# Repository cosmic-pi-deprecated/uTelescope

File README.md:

# uTelescope
A new mini detector developed during the GTI SDG summer school 2017

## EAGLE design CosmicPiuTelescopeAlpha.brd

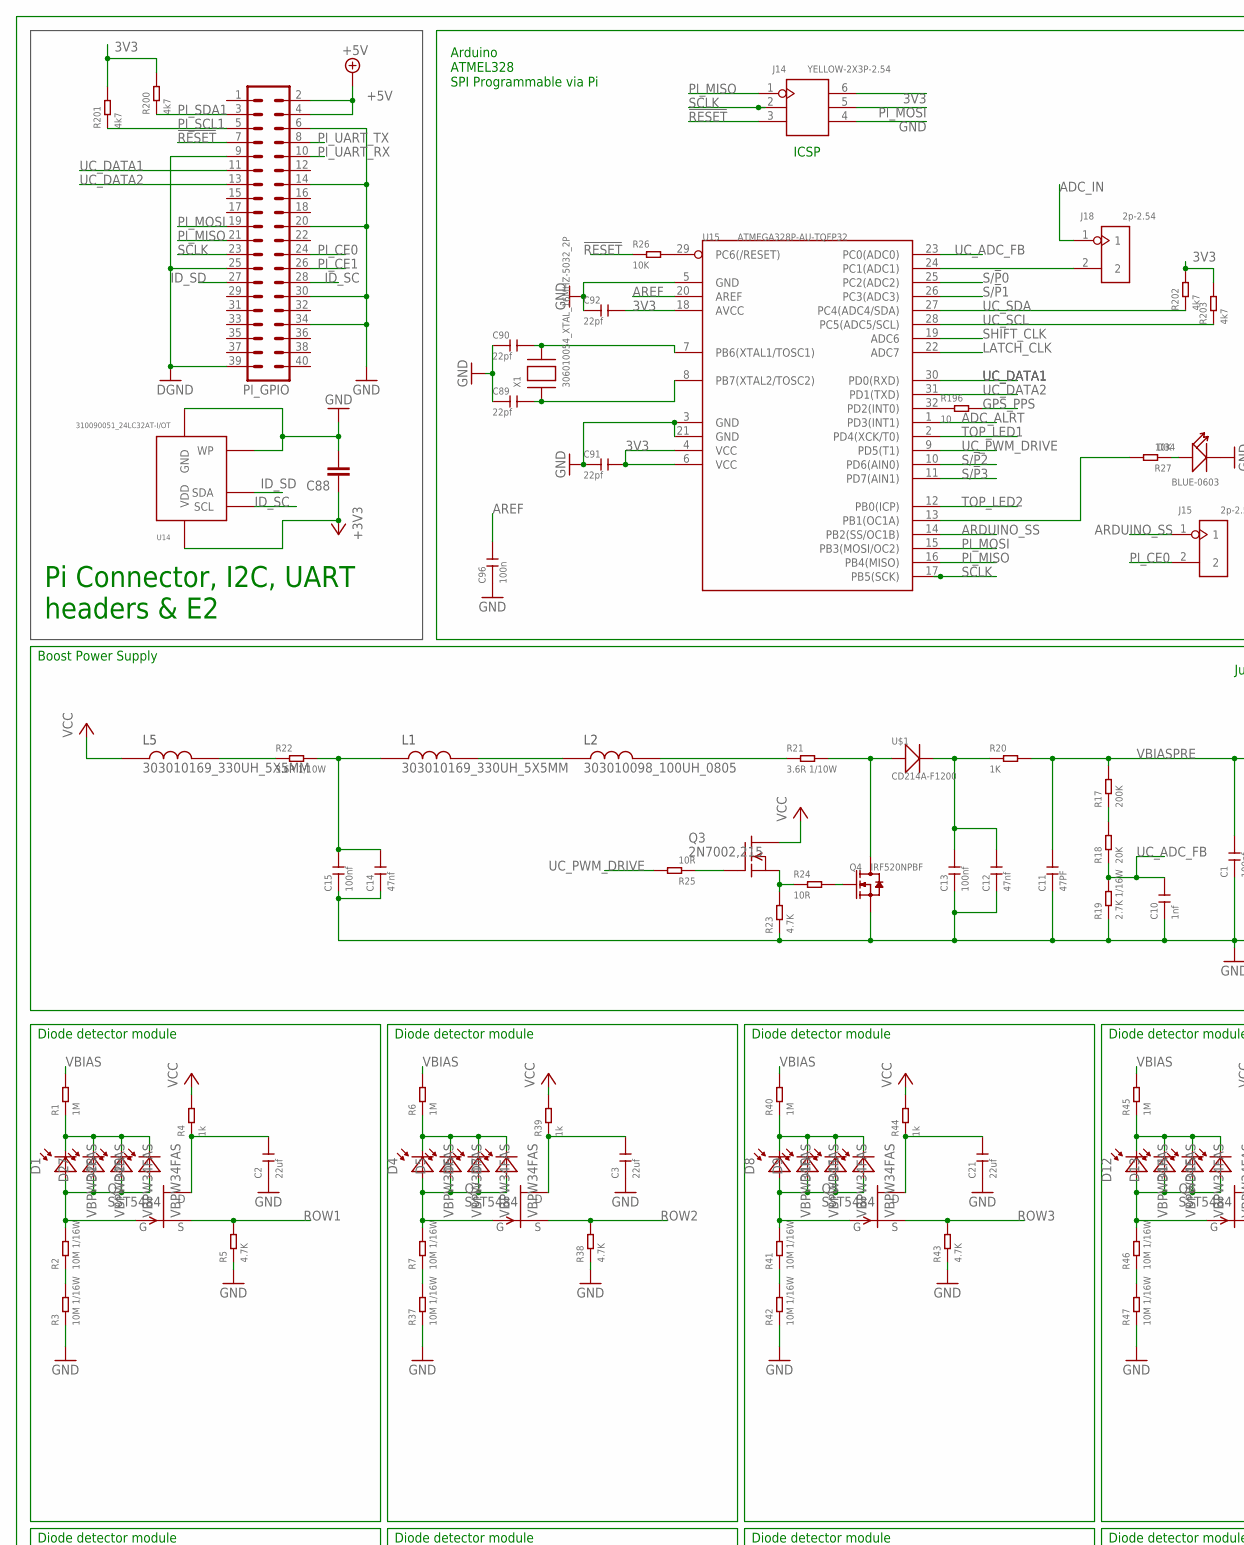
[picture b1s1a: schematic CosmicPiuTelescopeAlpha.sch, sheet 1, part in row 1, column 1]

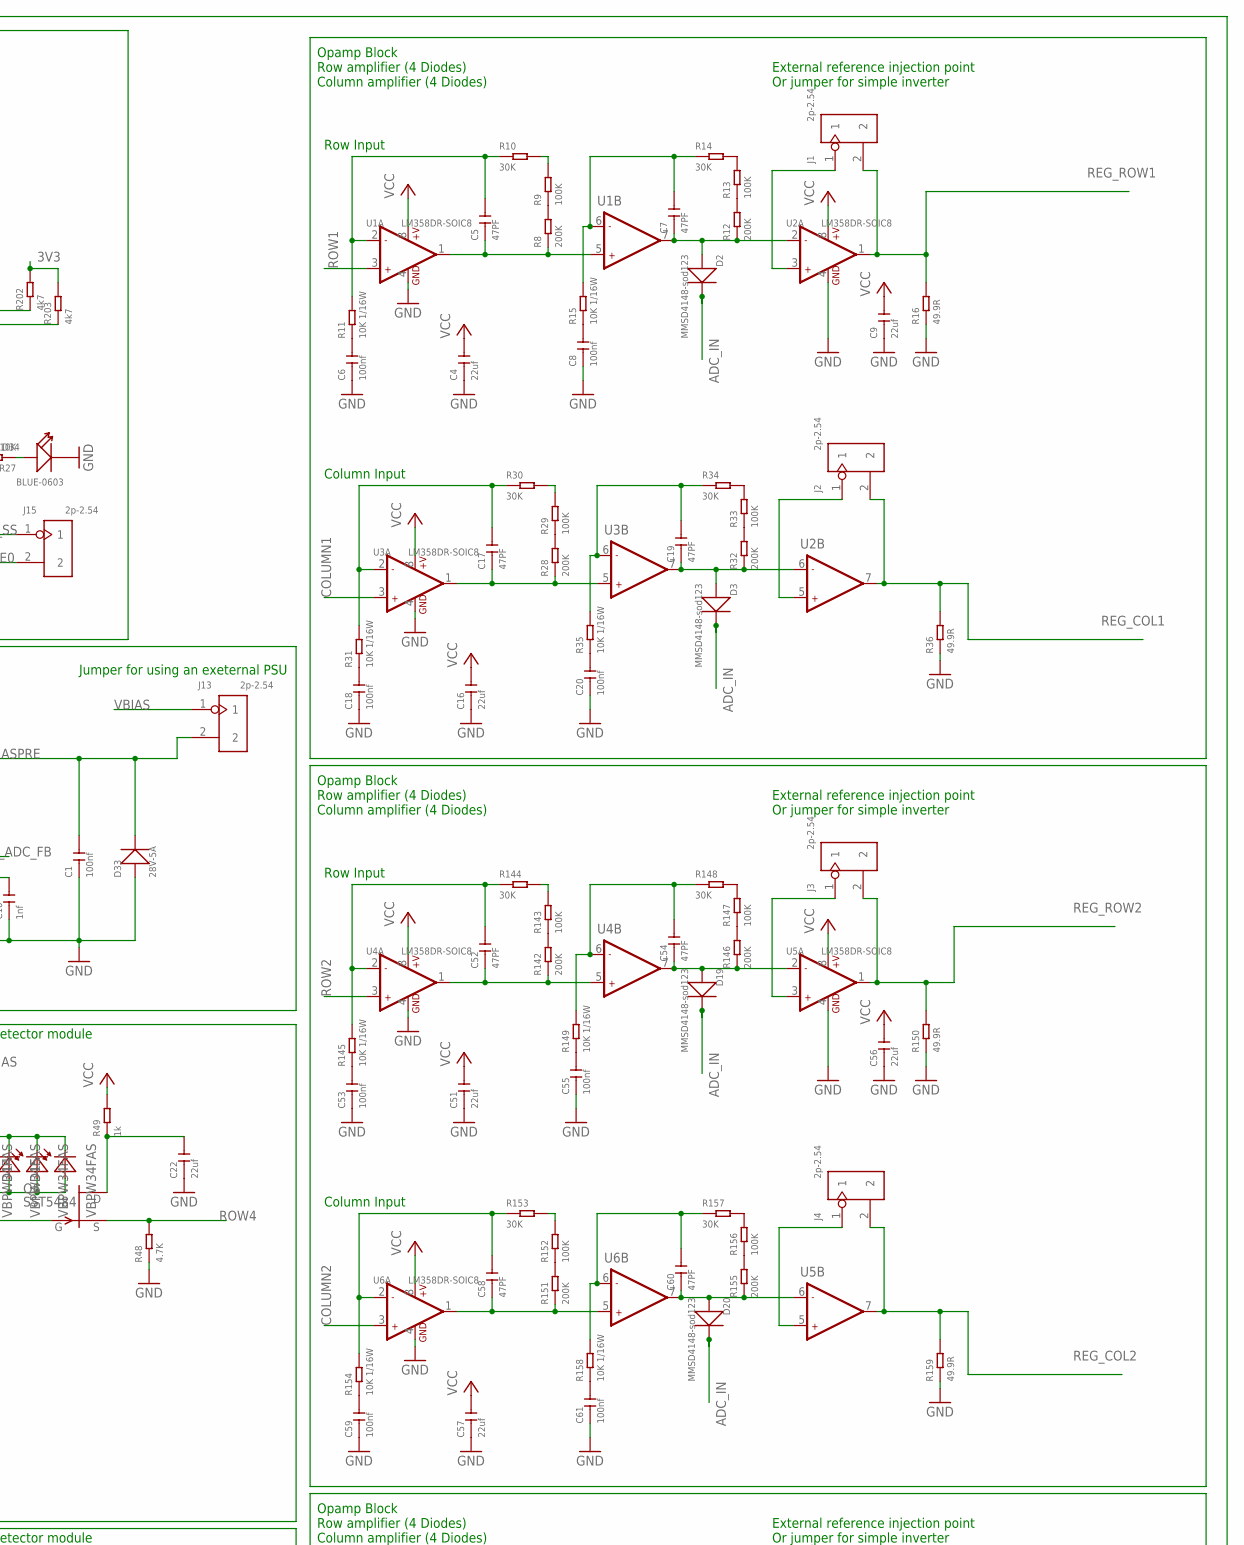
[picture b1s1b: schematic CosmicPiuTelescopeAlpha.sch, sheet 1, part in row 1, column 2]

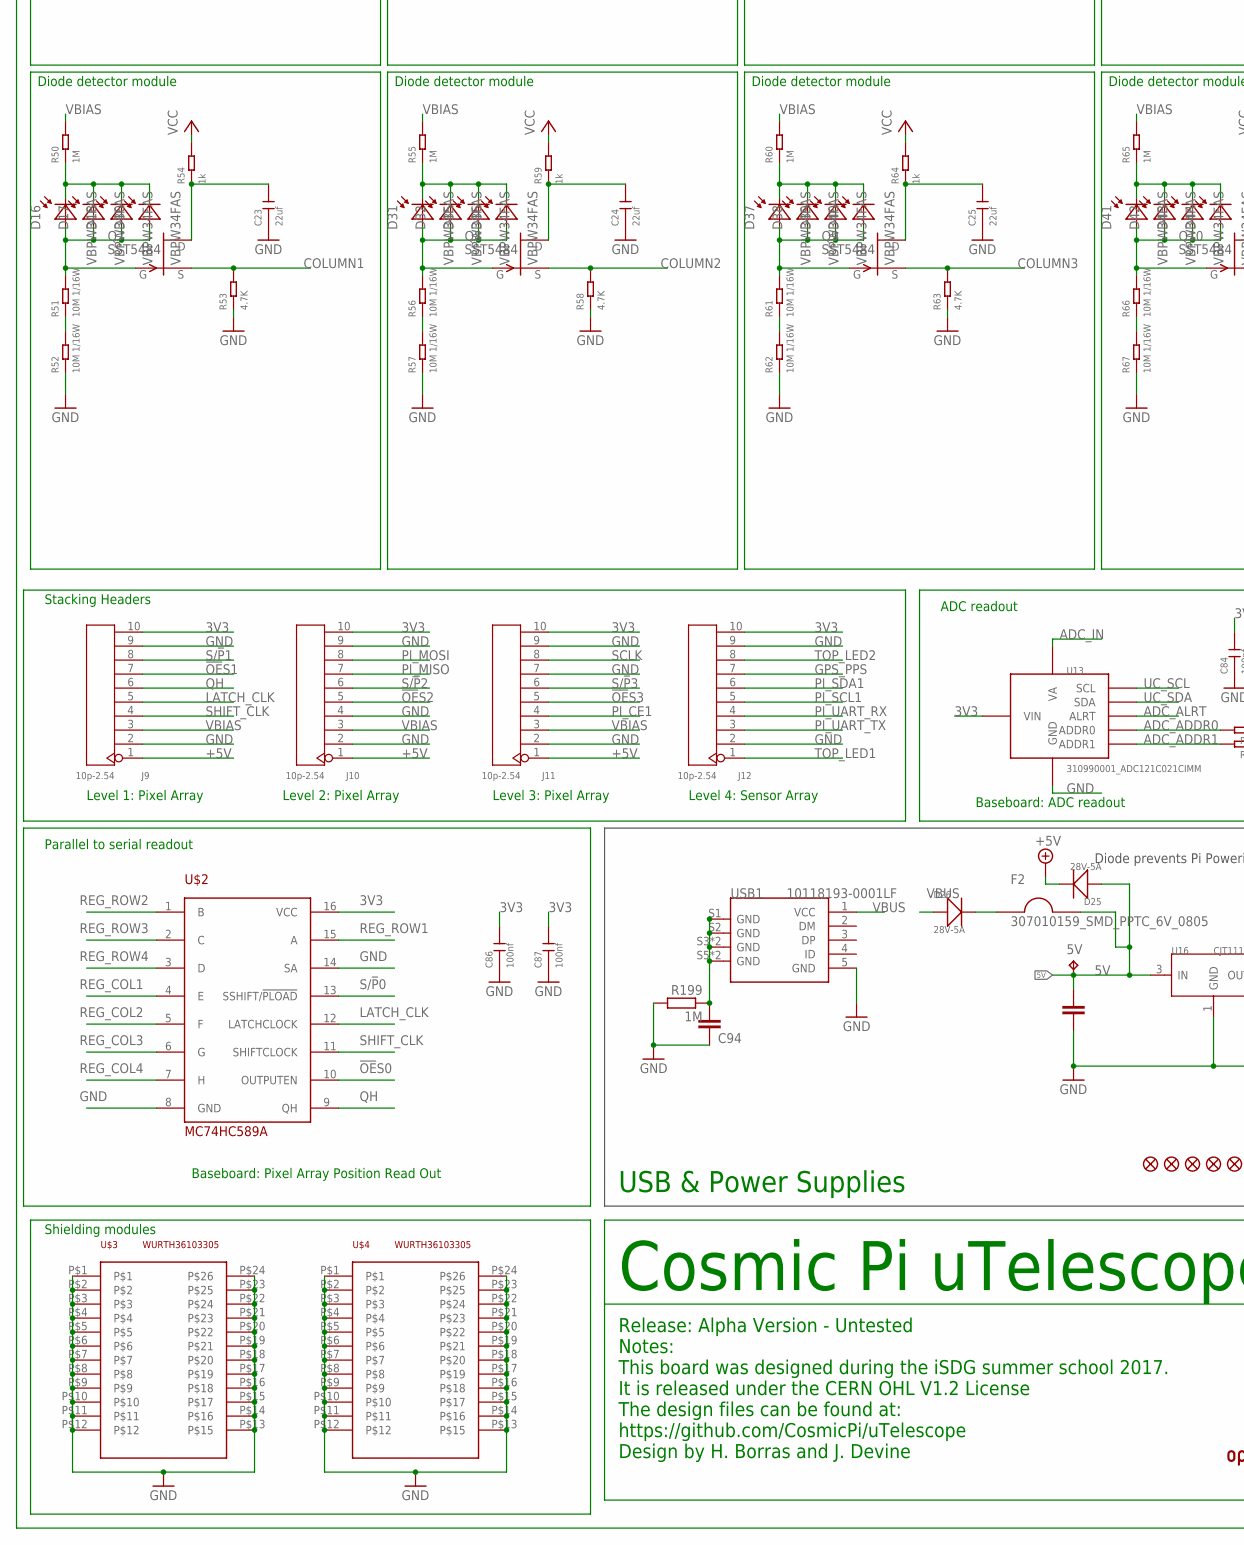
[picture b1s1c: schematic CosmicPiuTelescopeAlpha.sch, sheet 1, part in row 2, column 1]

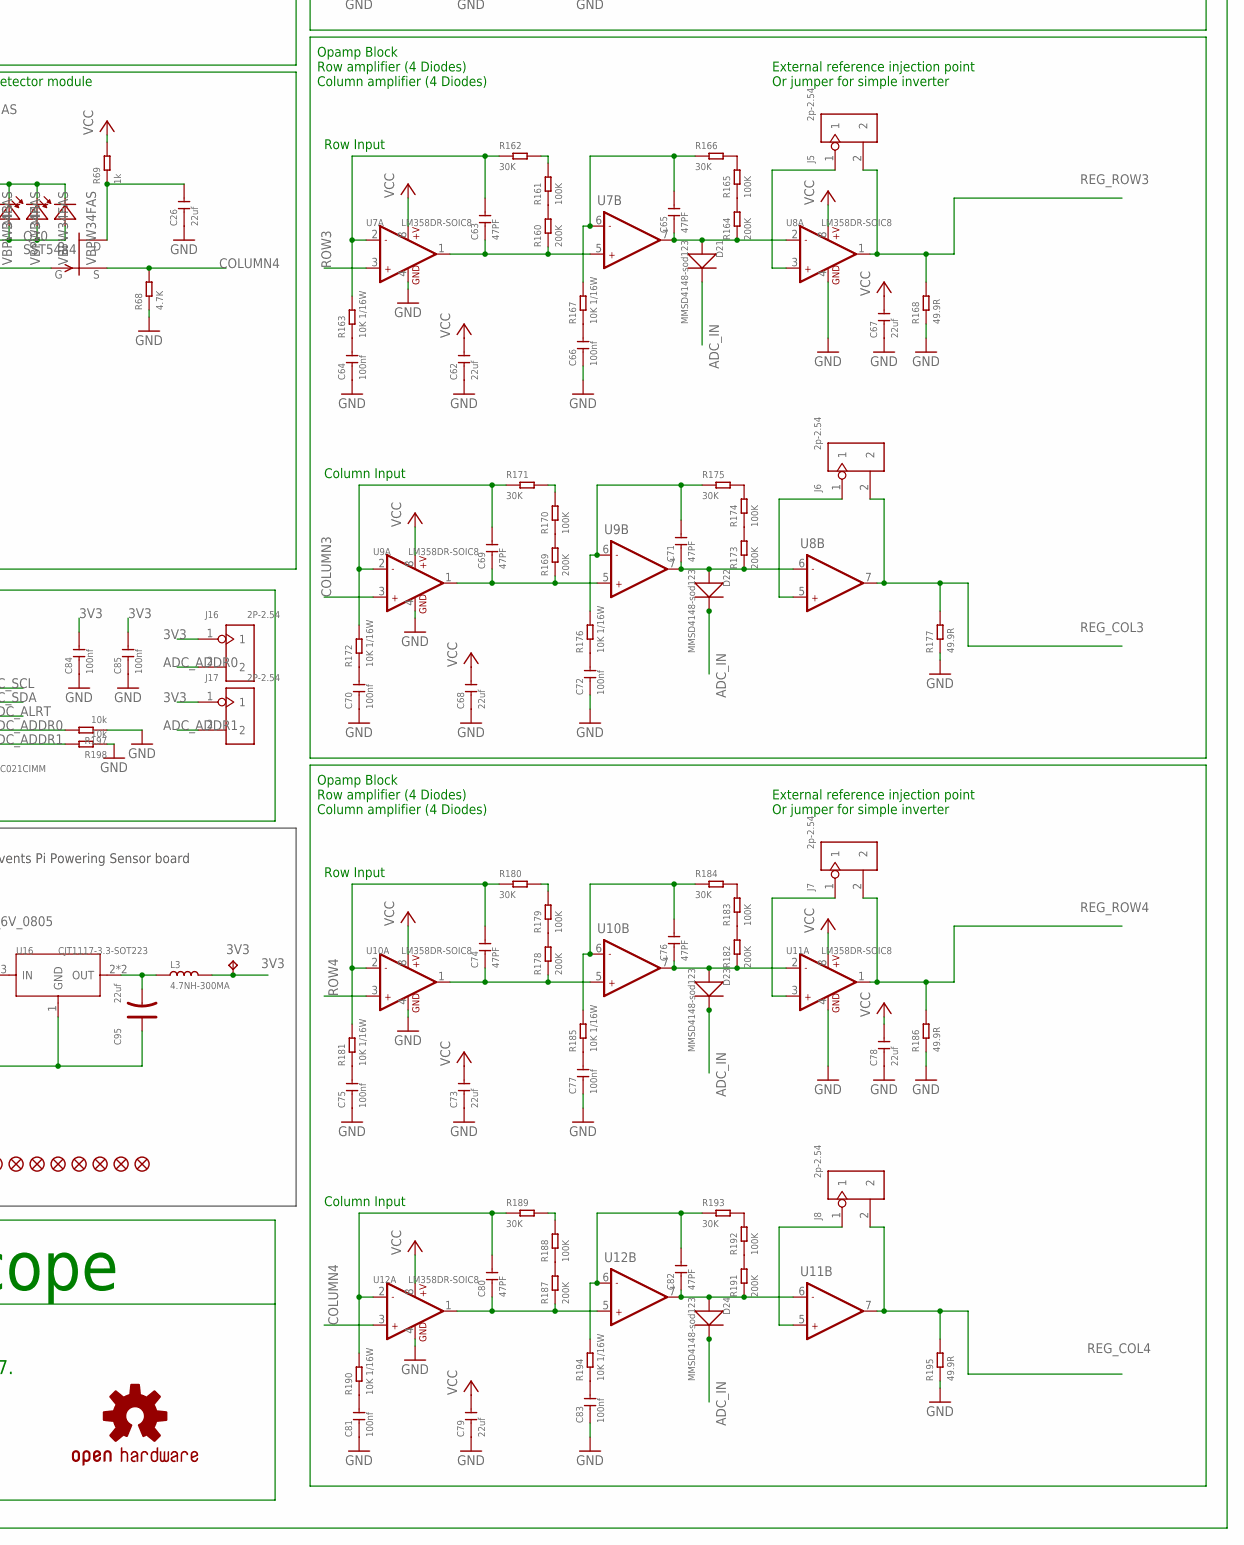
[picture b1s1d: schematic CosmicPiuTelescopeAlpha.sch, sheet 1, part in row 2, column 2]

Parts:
3V3, 5V: TPB1,27; B1,27
C1, C13, C15: 100nf; C0603
C2, C3, C21, C22, C23, C24, C25, C26: 22uf; C1206
C4, C9, C16, C51, C56, C57, C62, C67, C68, C73, C78, C79: 22uf; C0805
C5, C7, C11, C17, C19, C52, C54, C58, C60, C63, C65, C69, C71, C74, C76, C80, C82: 47PF; C0402
C6, C8, C18, C20, C53, C55, C59, C61, C64, C66, C70, C72, C75, C77, C81, C83: 100nf; C0402
C10: 1nf; C0603
C12, C14: 47nf; C0402
C84, C85, C86, C87: 100nf; C1206
C88, C94: C-EUC0402; C0402
C89, C90, C91, C92: 22pf; C0603
C93: 47uF; 1206
C95: 22uf; AVX-B
C96: 100n; C0603
D1, D4, D5, D6, D7, D8, D9, D10, D11, D12, D13, D14, D15, D16, D17, D18, D27, D28, D29, D30, D31, D32, D35, D36, D37, D38, D39, D40, D41, D42, D43, D44: VBPW34FAS; SOD6439X130N
D2, D3, D19, D20, D21, D22, D23, D24: MMSD4148-sod123; SOD-123
D25, D26, D33: 28V-5A; DO-214AA
D34: BLUE-0603; LED-0603
F2: 307010159_SMD_PPTC_6V_0805; F0805
FD1, FD2, FD3, FD4, FD5, FD6, FD7, FD8: FIDUCIAL1X2; FIDUCIAL-1X2
J1, J2, J3, J4, J5, J6, J7, J8, J13, J15, J18: 2p-2.54; H2-2.54
J9, J10, J11, J12: 10p-2.54; H10-2.54
J14: YELLOW-2X3P-2.54; H2X3-2.54
J16, J17: 2P-2.54; H2-2.54
L1, L5: 303010169_330UH_5X5MM; L2018
L2: 303010098_100UH_0805; L0805
L3: 4.7NH-300MA; L0402
LOGO1: OSHW-LOGOL; OSHW-LOGO-L
PI_GPIO: MA20-2
Q1, Q2, Q5, Q6, Q7, Q8, Q9, Q10: SST5484; SOT23
Q3: 2N7002,215; SOT23
Q4: IRF520NPBF; TO-220
R1, R6, R40, R45, R50, R55, R60, R65, R199: 1M; R0402
R2, R3, R7, R37, R41, R42, R46, R47, R51, R52, R56, R57, R61, R62, R66, R67: 10M 1/16W; R0402
R4, R39, R44, R49, R54, R59, R64, R69: 1k; R0402
R5, R38, R43, R48, R53, R58, R63, R68: 4.7K; R0402
R8, R12, R17, R28, R32, R142, R146, R151, R155, R160, R164, R169, R173, R178, R182, R187, R191: 200K; R0603
R9, R13, R29, R33, R143, R147, R152, R156, R161, R165, R170, R174, R179, R183, R188, R192: 100K; R0402
R10, R14, R30, R34, R144, R148, R153, R157, R162, R166, R171, R175, R180, R184, R189, R193: 30K; R0603
R11, R15, R31, R35, R145, R149, R154, R158, R163, R167, R172, R176, R181, R185, R190, R194: 10K 1/16W; R0402
R16, R36, R150, R159, R168, R177, R186, R195: 49.9R; R0402
R18: 20K; R0603
R19: 2.7K 1/16W; R0402
R20: 1K; R0603
R21, R22: 3.6R 1/10W; R0603
R23: 4.7K; R0805
R24, R25: 10R; R0603
R26, R27: 10K; R0603
R196: 10; R0603
R197, R198: 10k; R0402
R200, R201, R202, R203: 4k7; R0603
U1, U2, U3, U4, U5, U6, U7, U8, U9, U10, U11, U12: LM358DR-SOIC8; SOIC8-1.27-5X4MM
U13: 310990001_ADC121C021CIMM; VSSOP8
U14: 310090051_24LC32AT-I/OT; SOT235
U15: ATMEGA328P-AU-TQFP32; TQFP32-0.8-7X7MM
U16: CJT1117-3.3-SOT223; SOT-223
U$1: CD214A-F1200; DIOM8059X265N
U$2: MC74HC589A; SOIC127P600X175-16N
U$3, U$4: WURTH36103305; 36103305
USB1: 10118193-0001LF; MICRO-USB5+6P-SMD-0.65-B
X1: 306010054_XTAL_16MHZ-5032_2P; X5032_2P

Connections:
3V3: 3V3.TP, C84.2, C85.2, C86.2, C87.2, C88.1, C91.2, C92.2, J9.10, J10.10, J11.10, J12.10, J14.6, J16.1, J17.1, L3.2, R200.2, R201.2, R202.2, R203.2, U13.P$4 (VIN), U14.4 (VDD), U15.4 (VCC), U15.6 (VCC), U15.18 (AVCC), U$2.16 (VCC)
5V: 5V.TP, C93.1, D25.+, F2.P$2, U16.3 (IN)
!OE!S0: U$2.10 (OUTPUTEN)
!OE!S1: J9.7
!OE!S2: J10.5
!OE!S3: J11.5
!RESET: J14.3, PI_GPIO.7, R26.1
+5V: C4.2, C9.2, C16.2, C51.2, C56.2, C57.2, C62.2, C67.2, C68.2, C73.2, C78.2, C79.2, D25.-, J9.1, J10.1, J11.1, L5.P$1, PI_GPIO.2, PI_GPIO.4, Q3.3 (D), R4.2, R39.2, R44.2, R49.2, R54.2, R59.2, R64.2, R69.2, U1.8 (+V), U2.8 (+V), U3.8 (+V), U4.8 (+V), U5.8 (+V), U6.8 (+V), U7.8 (+V), U8.8 (+V), U9.8 (+V), U10.8 (+V), U11.8 (+V), U12.8 (+V)
ADC_ADDR0: J16.2, R197.2, U13.P$3 (ADDR0)
ADC_ADDR1: J17.2, R198.2, U13.P$6 (ADDR1)
ADC_ALRT: U13.P$2 (ALRT), U15.1 (PD3(INT1))
ADC_IN: D2.-, D3.-, D19.-, D20.-, D21.-, D22.-, D23.-, D24.-, J18.1, U13.P$5 (VA)
ARDUINO_SS: J15.1, U15.14 (PB2(SS/OC1B))
AREF: C96.2, U15.20 (AREF)
COLUMN1: Q7.2 (S), R53.2, U3.3 (+IN1)
COLUMN2: Q8.2 (S), R58.2, U6.3 (+IN1)
COLUMN3: Q9.2 (S), R63.2, U9.3 (+IN1)
COLUMN4: Q10.2 (S), R68.2, U12.3 (+IN1)
GND: C1.1, C2.1, C3.1, C4.1, C6.1, C8.1, C9.1, C10.1, C11.1, C12.1, C13.1, C14.1, C15.1, C16.1, C18.1, C20.1, C21.1, C22.1, C23.1, C24.1, C25.1, C26.1, C51.1, C53.1, C55.1, C56.1, C57.1, C59.1, C61.1, C62.1, C64.1, C66.1, C67.1, C68.1, C70.1, C72.1, C73.1, C75.1, C77.1, C78.1, C79.1, C81.1, C83.1, C84.1, C85.1, C86.1, C87.1, C88.2, C89.1, C90.1, C91.1, C92.1, C93.2, C94.1, C95.+, C96.1, D33.+, D34.-, J9.2, J9.9, J10.2, J10.4, J10.9, J11.2, J11.7, J11.9, J12.2, J12.9, J14.4, PI_GPIO.6, PI_GPIO.9, PI_GPIO.14, PI_GPIO.20, PI_GPIO.25, PI_GPIO.30, PI_GPIO.34, PI_GPIO.39, Q4.2 (S), Q4.HEAT (S), R3.1, R5.1, R16.1, R19.1, R23.1, R36.1, R37.1, R38.1, R42.1, R43.1, R47.1, R48.1, R52.1, R53.1, R57.1, R58.1, R62.1, R63.1, R67.1, R68.1, R150.1, R159.1, R168.1, R177.1, R186.1, R195.1, R197.1, R198.1, R199.2, U1.4 (GND), U2.4 (GND), U3.4 (GND), U4.4 (GND), U5.4 (GND), U6.4 (GND), U7.4 (GND), U8.4 (GND), U9.4 (GND), U10.4 (GND), U11.4 (GND), U12.4 (GND), U13.P$7 (GND), U14.2 (GND), U14.5 (WP), U15.3 (GND), U15.5 (GND), U15.21 (GND), U16.1 (GND), U$2.8 (GND), U$2.14 (SA), U$3.P$1, U$3.P$2, U$3.P$3, U$3.P$4, U$3.P$5, U$3.P$6, U$3.P$7, U$3.P$8, U$3.P$9, U$3.P$10, U$3.P$11, U$3.P$12, U$3.P$13, U$3.P$14, U$3.P$15, U$3.P$16, U$3.P$17, U$3.P$18, U$3.P$19, U$3.P$20, U$3.P$21, U$3.P$22, U$3.P$23, U$3.P$24, U$4.P$1, U$4.P$2, U$4.P$3, U$4.P$4, U$4.P$5, U$4.P$6, U$4.P$7, U$4.P$8, U$4.P$9, U$4.P$10, U$4.P$11, U$4.P$12, U$4.P$13, U$4.P$14, U$4.P$15, U$4.P$16, U$4.P$17, U$4.P$18, U$4.P$19, U$4.P$20, U$4.P$21, U$4.P$22, U$4.P$23, U$4.P$24, USB1.5 (GND)
GPS_PPS: J12.7, R196.2
ID_SC: PI_GPIO.28, U14.1 (SCL)
ID_SD: PI_GPIO.27, U14.3 (SDA)
LATCH_CLK: J9.5, U15.22 (ADC7), U$2.12 (LATCHCLOCK)
unnamed: Q4.3 (D), R21.2, U$1.1 (+)
unnamed: D1.C, D27.C, D28.C, D29.C, R1.1
unnamed: D1.A, D27.A, D28.A, D29.A, Q1.3 (G), R2.2
unnamed: R2.1, R3.2
unnamed: C2.2, Q1.1 (D), R4.1
unnamed: R28.2, R29.1
unnamed: C18.2, R31.1
unnamed: D4.C, D5.C, D6.C, D7.C, R6.1
unnamed: R8.2, R9.1
unnamed: C6.2, R11.1
unnamed: C5.1, R8.1, U1.1 (OUT1), U1.5 (+IN2)
unnamed: R9.2, R10.2
unnamed: C5.2, R10.1, R11.2, U1.2 (-IN1)
unnamed: R12.2, R13.1
unnamed: C8.2, R15.1
unnamed: R13.2, R14.2
unnamed: C7.2, R14.1, R15.2, U1.6 (-IN2)
unnamed: D4.A, D5.A, D6.A, D7.A, Q2.3 (G), R7.2
unnamed: R7.1, R37.2
unnamed: C7.1, D2.+, R12.1, U1.7 (OUT2), U2.2 (-IN1)
unnamed: J1.1, U2.3 (+IN1)
unnamed: R17.1, R18.2
unnamed: C14.2, C15.2, L1.P$1, R22.2
unnamed: C12.2, C13.2, R20.1, U$1.2 (-)
unnamed: L5.P$2, R22.1
unnamed: L2.P$2, R21.1
unnamed: Q3.2 (S), R23.2, R24.1
unnamed: Q3.1 (G), R25.1
unnamed: L1.P$2, L2.P$1
unnamed: Q4.1 (G), R24.2
unnamed: C17.1, R28.1, U3.1 (OUT1), U3.5 (+IN2)
unnamed: R29.2, R30.2
unnamed: C17.2, R30.1, R31.2, U3.2 (-IN1)
unnamed: R32.2, R33.1
unnamed: C20.2, R35.1
unnamed: R33.2, R34.2
unnamed: C19.2, R34.1, R35.2, U3.6 (-IN2)
unnamed: C19.1, D3.+, R32.1, U2.6 (-IN2), U3.7 (OUT2)
unnamed: C3.2, Q2.1 (D), R39.1
unnamed: J2.1, U2.5 (+IN2)
unnamed: D8.C, D9.C, D10.C, D11.C, R40.1
unnamed: D8.A, D9.A, D10.A, D11.A, Q5.3 (G), R41.2
unnamed: R41.1, R42.2
unnamed: C21.2, Q5.1 (D), R44.1
unnamed: D12.C, D13.C, D14.C, D15.C, R45.1
unnamed: D12.A, D13.A, D14.A, D15.A, Q6.3 (G), R46.2
unnamed: R46.1, R47.2
unnamed: C22.2, Q6.1 (D), R49.1
unnamed: D16.C, D17.C, D18.C, D30.C, R50.1
unnamed: D16.A, D17.A, D18.A, D30.A, Q7.3 (G), R51.2
unnamed: R51.1, R52.2
unnamed: C23.2, Q7.1 (D), R54.1
unnamed: D31.C, D32.C, D35.C, D36.C, R55.1
unnamed: D31.A, D32.A, D35.A, D36.A, Q8.3 (G), R56.2
unnamed: R56.1, R57.2
unnamed: C24.2, Q8.1 (D), R59.1
unnamed: D37.C, D38.C, D39.C, D40.C, R60.1
unnamed: D37.A, D38.A, D39.A, D40.A, Q9.3 (G), R61.2
unnamed: R61.1, R62.2
unnamed: C25.2, Q9.1 (D), R64.1
unnamed: D41.C, D42.C, D43.C, D44.C, R65.1
unnamed: D41.A, D42.A, D43.A, D44.A, Q10.3 (G), R66.2
unnamed: R66.1, R67.2
unnamed: C26.2, Q10.1 (D), R69.1
unnamed: R142.2, R143.1
unnamed: C53.2, R145.1
unnamed: C52.1, R142.1, U4.1 (OUT1), U4.5 (+IN2)
unnamed: R143.2, R144.2
unnamed: C52.2, R144.1, R145.2, U4.2 (-IN1)
unnamed: R146.2, R147.1
unnamed: C55.2, R149.1
unnamed: R147.2, R148.2
unnamed: C54.2, R148.1, R149.2, U4.6 (-IN2)
unnamed: C54.1, D19.+, R146.1, U4.7 (OUT2), U5.2 (-IN1)
unnamed: J3.1, U5.3 (+IN1)
unnamed: R151.2, R152.1
unnamed: C59.2, R154.1
unnamed: C58.1, R151.1, U6.1 (OUT1), U6.5 (+IN2)
unnamed: R152.2, R153.2
unnamed: C58.2, R153.1, R154.2, U6.2 (-IN1)
unnamed: R155.2, R156.1
unnamed: C61.2, R158.1
unnamed: R156.2, R157.2
unnamed: C60.2, R157.1, R158.2, U6.6 (-IN2)
unnamed: C60.1, D20.+, R155.1, U5.6 (-IN2), U6.7 (OUT2)
unnamed: J4.1, U5.5 (+IN2)
unnamed: C94.2, R199.1, USB1.S1 (GND), USB1.S2 (GND), USB1.S3 (GND), USB1.S4 (GND), USB1.S5 (GND), USB1.S6 (GND)
unnamed: R160.2, R161.1
unnamed: C64.2, R163.1
unnamed: C63.1, R160.1, U7.1 (OUT1), U7.5 (+IN2)
unnamed: R161.2, R162.2
unnamed: C63.2, R162.1, R163.2, U7.2 (-IN1)
unnamed: R164.2, R165.1
unnamed: C66.2, R167.1
unnamed: R165.2, R166.2
unnamed: C65.2, R166.1, R167.2, U7.6 (-IN2)
unnamed: C65.1, D21.+, R164.1, U7.7 (OUT2), U8.2 (-IN1)
unnamed: D26.-, F2.P$1
unnamed: J5.1, U8.3 (+IN1)
unnamed: R169.2, R170.1
unnamed: C70.2, R172.1
unnamed: C69.1, R169.1, U9.1 (OUT1), U9.5 (+IN2)
unnamed: R170.2, R171.2
unnamed: C69.2, R171.1, R172.2, U9.2 (-IN1)
unnamed: R173.2, R174.1
unnamed: C72.2, R176.1
unnamed: R174.2, R175.2
unnamed: C71.2, R175.1, R176.2, U9.6 (-IN2)
unnamed: C71.1, D22.+, R173.1, U8.6 (-IN2), U9.7 (OUT2)
unnamed: J6.1, U8.5 (+IN2)
unnamed: C95.-, L3.1, U16.2 (OUT), U16.TER (OUT)
unnamed: R178.2, R179.1
unnamed: C75.2, R181.1
unnamed: C74.1, R178.1, U10.1 (OUT1), U10.5 (+IN2)
unnamed: R179.2, R180.2
unnamed: C74.2, R180.1, R181.2, U10.2 (-IN1)
unnamed: R182.2, R183.1
unnamed: C77.2, R185.1
unnamed: R183.2, R184.2
unnamed: C76.2, R184.1, R185.2, U10.6 (-IN2)
unnamed: C76.1, D23.+, R182.1, U10.7 (OUT2), U11.2 (-IN1)
unnamed: R27.2, U15.13 (PB1(OC1A))
unnamed: J7.1, U11.3 (+IN1)
unnamed: R187.2, R188.1
unnamed: C81.2, R190.1
unnamed: C80.1, R187.1, U12.1 (OUT1), U12.5 (+IN2)
unnamed: R188.2, R189.2
unnamed: C80.2, R189.1, R190.2, U12.2 (-IN1)
unnamed: R191.2, R192.1
unnamed: C83.2, R194.1
unnamed: R192.2, R193.2
unnamed: C82.2, R193.1, R194.2, U12.6 (-IN2)
unnamed: C82.1, D24.+, R191.1, U11.6 (-IN2), U12.7 (OUT2)
unnamed: J8.1, U11.5 (+IN2)
unnamed: J18.2, U15.24 (PC1(ADC1))
unnamed: R26.2, U15.29 (PC6(/RESET))
unnamed: D34.+, R27.1
unnamed: C90.2, U15.7 (PB6(XTAL1/TOSC1)), X1.P$2
unnamed: C89.2, U15.8 (PB7(XTAL2/TOSC2)), X1.P$1
unnamed: R196.1, U15.32 (PD2(INT0))
PI_CE0: J15.2, PI_GPIO.24
PI_CE1: J11.4, PI_GPIO.26
PI_MISO: J10.7, J14.1, PI_GPIO.21, U15.16 (PB4(MISO))
PI_MOSI: J10.8, J14.5, PI_GPIO.19, U15.15 (PB3(MOSI/OC2))
PI_SCL1: J12.5, PI_GPIO.5, R201.1
PI_SDA1: J12.6, PI_GPIO.3, R200.1
PI_UART_RX: J12.4, PI_GPIO.10
PI_UART_TX: J12.3, PI_GPIO.8
QH: J9.6, U$2.9 (QH)
REG_COL1: J2.2, R36.2, U2.7 (OUT2), U$2.4 (E)
REG_COL2: J4.2, R159.2, U5.7 (OUT2), U$2.5 (F)
REG_COL3: J6.2, R177.2, U8.7 (OUT2), U$2.6 (G)
REG_COL4: J8.2, R195.2, U11.7 (OUT2), U$2.7 (H)
REG_ROW1: J1.2, R16.2, U2.1 (OUT1), U$2.15 (A)
REG_ROW2: J3.2, R150.2, U5.1 (OUT1), U$2.1 (B)
REG_ROW3: J5.2, R168.2, U8.1 (OUT1), U$2.2 (C)
REG_ROW4: J7.2, R186.2, U11.1 (OUT1), U$2.3 (D)
ROW1: Q1.2 (S), R5.2, U1.3 (+IN1)
ROW2: Q2.2 (S), R38.2, U4.3 (+IN1)
ROW3: Q5.2 (S), R43.2, U7.3 (+IN1)
ROW4: Q6.2 (S), R48.2, U10.3 (+IN1)
S/!P!0: U15.25 (PC2(ADC2)), U$2.13 (SSHIFT/!PLOAD)
S/!P!1: J9.8, U15.26 (PC3(ADC3))
S/!P!2: J10.6, U15.10 (PD6(AIN0))
S/!P!3: J11.6, U15.11 (PD7(AIN1))
SCLK: J11.8, J14.2, PI_GPIO.23, U15.17 (PB5(SCK))
SHIFT_CLK: J9.4, U15.19 (ADC6), U$2.11 (SHIFTCLOCK)
TOP_LED1: J12.1, U15.2 (PD4(XCK/T0))
TOP_LED2: J12.8, U15.12 (PB0(ICP))
UC_ADC_FB: C10.2, R18.1, R19.2, U15.23 (PC0(ADC0))
UC_DATA1: PI_GPIO.11, U15.30 (PD0(RXD))
UC_DATA2: PI_GPIO.13, U15.31 (PD1(TXD))
UC_PWM_DRIVE: R25.2, U15.9 (PD5(T1))
UC_SCL: R203.1, U13.P$1 (SCL), U15.28 (PC5(ADC5/SCL))
UC_SDA: R202.1, U13.P$8 (SDA), U15.27 (PC4(ADC4/SDA))
VBIAS: J9.3, J10.3, J11.3, J13.1, R1.2, R6.2, R40.2, R45.2, R50.2, R55.2, R60.2, R65.2
VBIASPRE: C1.2, C11.2, D33.-, J13.2, R17.2, R20.2
VBUS: D26.+, USB1.1 (VCC)

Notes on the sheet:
External reference injection point Or jumper for simple inverter
Boost Power Supply
Diode detector module
Opamp Block Row amplifier (4 Diodes) Column amplifier (4 Diodes)
Row Input
Column Input
Stacking Headers
Level 1: Pixel Array
Level 2: Pixel Array
Level 3: Pixel Array
Level 4: Sensor Array
Parallel to serial readout
Baseboard: Pixel Array Position Read Out
ADC readout
Baseboard: ADC readout
Jumper for using an exeternal PSU
Pi Connector, I2C, UART headers & E2
Diode prevents Pi Powering Sensor board
USB & Power Supplies
Arduino ATMEL328 SPI Programmable via Pi
ICSP
Shielding modules
Cosmic Pi uTelescope
Release: Alpha Version - Untested Notes: This board was designed during the iSDG summer school 2017. It is released under the CERN OHL V1.2 License The design files can be found at: https://github.com/CosmicPi/uTelescope Design by H. Borras and J. Devine

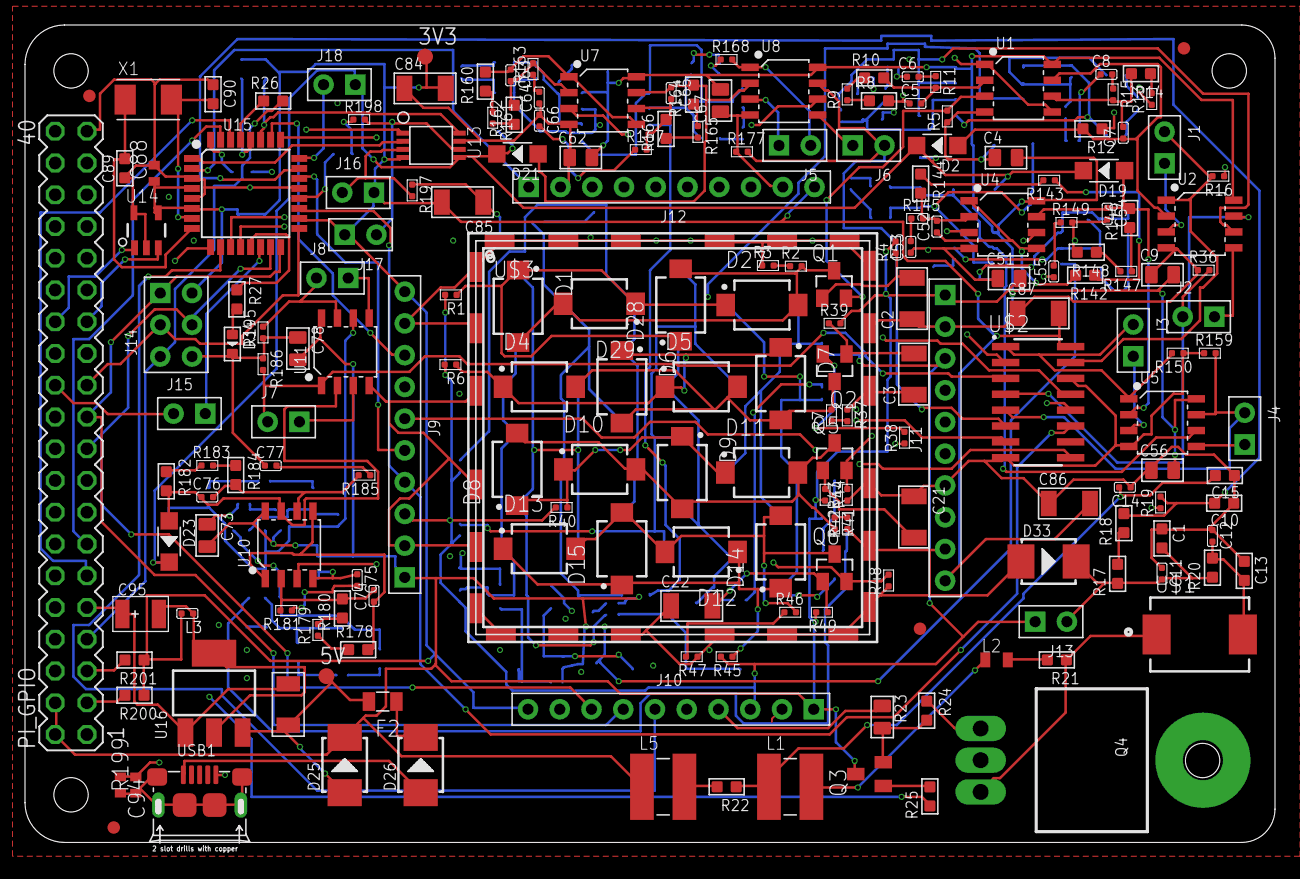
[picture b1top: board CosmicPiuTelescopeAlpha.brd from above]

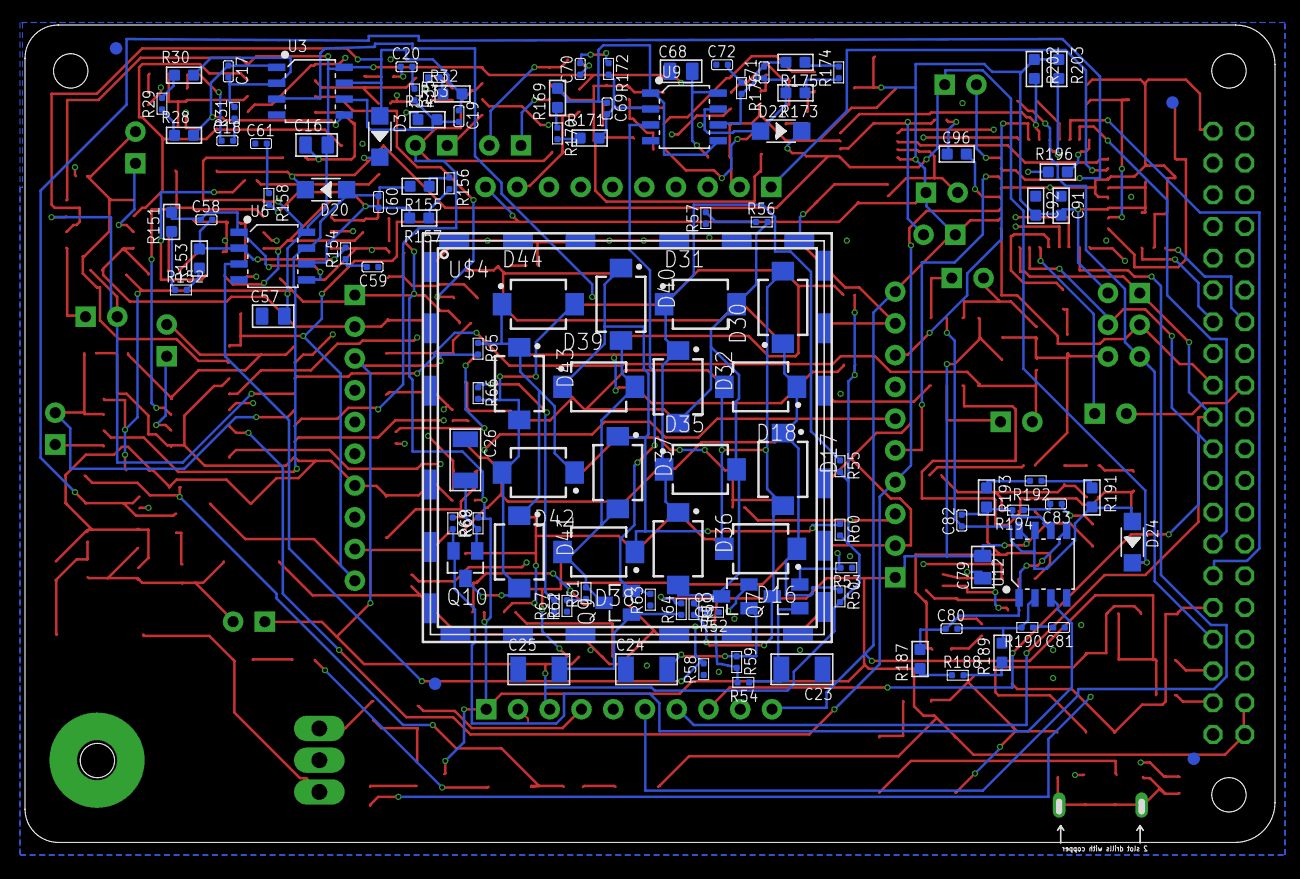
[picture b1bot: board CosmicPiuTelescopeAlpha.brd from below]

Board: 4 copper layers, 100.0 x 65.4 mm, 314 parts (115 on the bottom side), 197 nets.

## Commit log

2017-09-08 First upload.
    Hardware is currently being produced, so far it's 100% untested!
2017-09-08 BOM for prototype production via SEEED
2018-01-08 4k7 part swapped for 1k on R4,R39,R44,R49,R54,R59,R64,R69
    This was a mistake in the BOM, the schematic is correct.

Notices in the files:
CosmicPiuTelescopeAlpha.brd:
Licensed under CERN OHL V1.2
parts and their libraries:
SparkFun-Aesthetics: Licensing: Creative Commons ShareAlike 4.0 International - https://creativecommons.org/licenses/by-sa/4.0
